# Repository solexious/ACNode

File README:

A design for the london hackspace tool access control system: http://wiki.london.hackspace.org.uk/view/Project:Tool_Access_Control

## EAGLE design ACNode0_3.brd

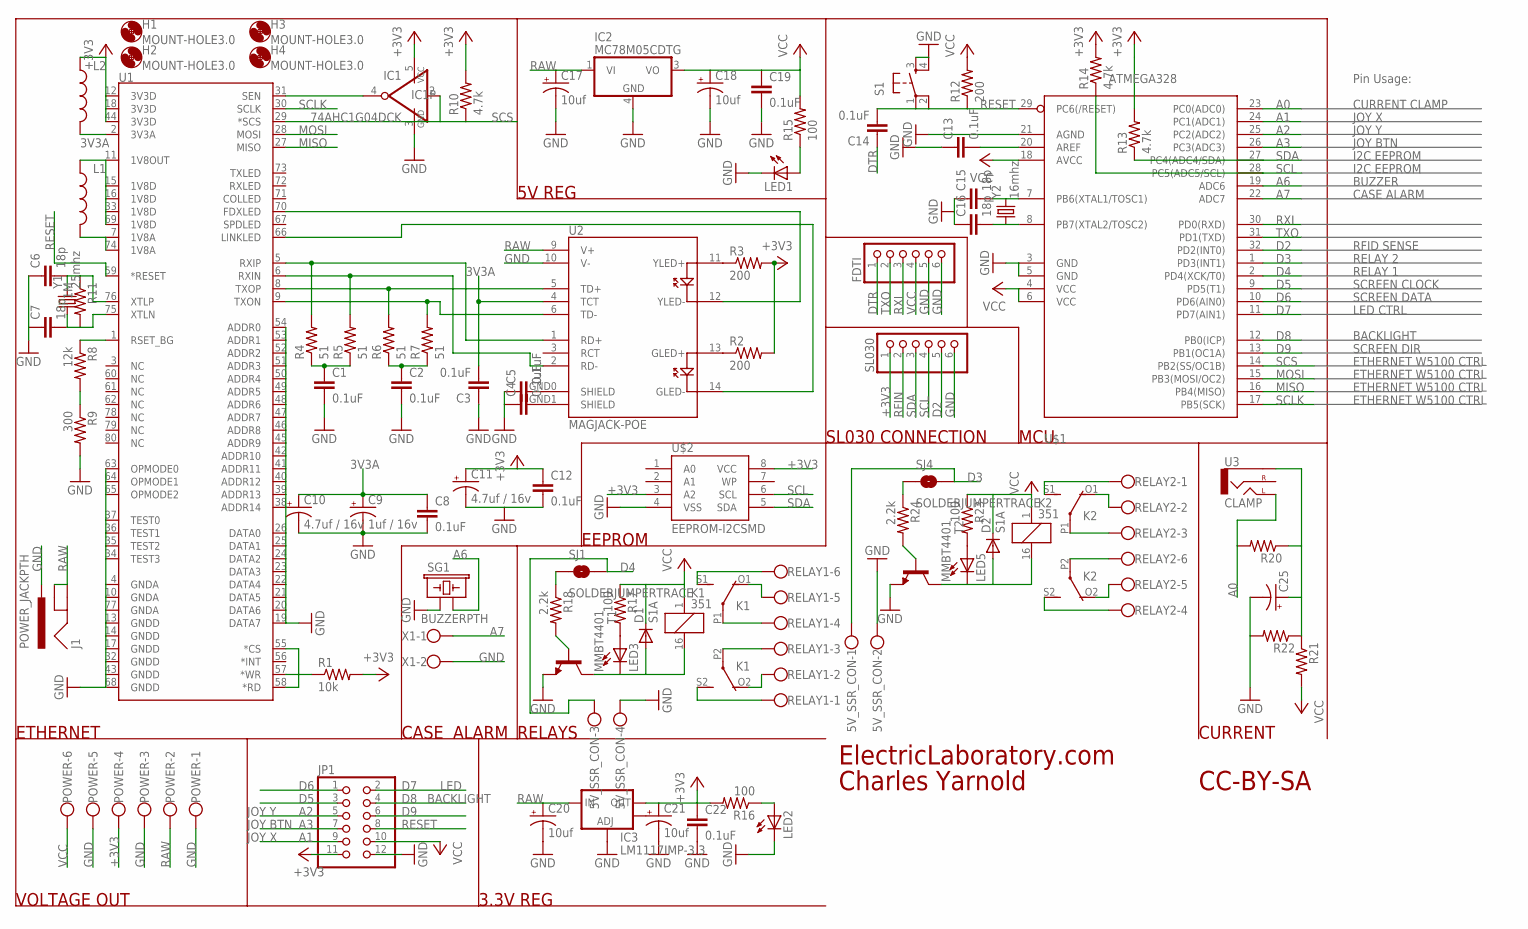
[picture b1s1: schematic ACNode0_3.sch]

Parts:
5V_SSR_CON: W237-4
C1, C2, C3, C4, C5, C8, C12, C13, C14, C19, C22: 0.1uF; 0603-CAP
C6, C7, C15, C16: 18p; 0603-CAP
C9: 1uf / 16v; EIA3216
C10, C11: 4.7uf / 16v; EIA3216
C17, C18, C20, C21: 10uf; EIA3216
C25: CAP_POL1206; EIA3216
D1, D2: S1A; DO-214AC
FDTI: PINHD-1X6; 1X06
H1, H2, H3, H4: MOUNT-HOLE3.0; 3,0
IC1: 74AHC1G04DCK; SC70-5
IC2: MC78M05CDTG; DPACK_3
IC3: LM1117IMP-3.3; SOT223
J1: POWER_JACKPTH; POWER_JACK_PTH
JP1: PINHD-2X6; 2X06
K1, K2: 351
L1, L2: INDUCTOR1206H*; INDUCTOR-1206
LED1, LED2, LED3, LED5: LED0603; LED-0603
POWER: W237-6
R1: 10k; 0603-RES
R2, R3, R12: 200; 0603-RES
R4, R5, R6, R7: 51; 0603-RES
R8: 12k; 0603-RES
R9: 300; 0603-RES
R10, R13, R14: 4.7k; 0603-RES
R11: 1M; 0603-RES
R15, R16, R17, R23: 100; 0603-RES
R18, R24: 2.2k; 0603-RES
R20, R21, R22: RESISTOR0603-RES; 0603-RES
RELAY1, RELAY2: W237-6
S1: TAC_SWITCHSMD; TACTILE_SWITCH_SMD
SG1: BUZZERPTH; BUZZER-12MM
SJ1, SJ4: SOLDERJUMPERTRACE; SJ_2S-TRACE
SL030: PINHD-1X6; 1X06
T1, T2: MMBT4401; SOT23-BEC
U1: W5100; LQFP-80
U2: MAGJACK-POE
U3: CLAMP; AUDIO-JACK
U$1: ATMEGA328; TQFP32-08
U$2: EEPROM-I2CSMD; SO08
X1: W237-102
Y1: 25mhz; HC49UP
Y2: 16mhz; HC49UP

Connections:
3V3A: C3.2, C8.1, C9.A (+), C10.A (+), L2.P$2 (2), U1.2 (3V3A), U2.4 (TCT)
+3V3: C11.A (+), C12.1, C21.A (+), C22.1, IC1.5 (VCC), IC3.2 (OUT), JP1.11, L2.P$1 (1), POWER.4, R1.2, R2.2, R3.2, R10.2, R13.2, R14.2, R16.2, SL030.1, U1.12 (3V3D), U1.18 (3V3D), U1.44 (3V3D), U$2.3 (A2), U$2.8 (VCC)
A0: R20.2, U3.TIP (LEFT), U$1.23 (PC0(ADC0))
A1: JP1.9, U$1.24 (PC1(ADC1))
A2: JP1.5, U$1.25 (PC2(ADC2))
A3: JP1.7, U$1.26 (PC3(ADC3))
A6: SG1.- (2), U$1.19 (ADC6)
A7: U$1.22 (ADC7), X1.1
D2: SL030.5, U$1.32 (PD2(INT0))
D3: 5V_SSR_CON.1, SJ4.2, U$1.1 (PD3(INT1))
D4: 5V_SSR_CON.3, SJ1.2, U$1.2 (PD4(XCK/T0))
D5: JP1.3, U$1.9 (PD5(T1))
D6: JP1.1, U$1.10 (PD6(AIN0))
D7: JP1.2, U$1.11 (PD7(AIN1))
D8: JP1.4, U$1.12 (PB0(ICP))
D9: JP1.6, U$1.13 (PB1(OC1A))
DTR: C14.1, FDTI.1
GND: 5V_SSR_CON.2, 5V_SSR_CON.4, C1.2, C2.2, C3.1, C4.1, C5.1, C6.1, C7.1, C8.2, C9.C (-), C10.C (-), C11.C (-), C12.2, C13.1, C15.1, C16.1, C17.C (-), C18.C (-), C19.2, C20.C (-), C21.C (-), C22.2, C25.C (-), FDTI.5, FDTI.6, IC1.3 (GND), IC2.4 (GND), IC3.1 (ADJ), J1.PWR, JP1.12, LED1.C, LED2.C, POWER.1, POWER.3, POWER.5, R9.2, R22.2, S1.3, S1.4, SG1.+ (1), SL030.6, T1.E, T2.E, U1.4 (GNDA), U1.10 (GNDA), U1.13 (GNDD), U1.14 (GNDD), U1.17 (GNDD), U1.19 (DATA7), U1.20 (DATA6), U1.21 (DATA5), U1.22 (DATA4), U1.23 (DATA3), U1.24 (DATA2), U1.25 (DATA1), U1.26 (DATA0), U1.32 (GNDD), U1.34 (TEST3), U1.35 (TEST2), U1.36 (TEST1), U1.37 (TEST0), U1.38 (ADDR14), U1.39 (ADDR13), U1.40 (ADDR12), U1.41 (ADDR11), U1.42 (ADDR10), U1.43 (GNDD), U1.45 (ADDR9), U1.46 (ADDR8), U1.47 (ADDR7), U1.48 (ADDR6), U1.49 (ADDR5), U1.50 (ADDR4), U1.51 (ADDR3), U1.52 (ADDR2), U1.53 (ADDR1), U1.54 (ADDR0), U1.63 (OPMODE0), U1.64 (OPMODE1), U1.65 (OPMODE2), U1.68 (GNDD), U1.77 (GNDA), U2.10 (V-), U$1.3 (GND), U$1.5 (GND), U$1.21 (AGND), U$2.4 (VSS), X1.2
MISO: U1.27 (MISO), U$1.16 (PB4(MISO))
MOSI: U1.28 (MOSI), U$1.15 (PB3(MOSI/OC2))
unnamed: IC1.4 (O), U1.31 (SEN)
unnamed: C13.2, U$1.20 (AREF)
unnamed: C2.1, R6.1, R7.1
unnamed: C1.1, R4.1, R5.1
unnamed: L1.P$2 (2), U1.7 (1V8A), U1.74 (1V8A)
unnamed: L1.P$1 (1), U1.11 (1V8OUT), U1.15 (1V8D), U1.16 (1V8D), U1.33 (1V8D), U1.69 (1V8D)
unnamed: R1.1, U1.55 (*CS), U1.57 (*WR), U1.58 (*RD)
unnamed: R8.2, R9.1
unnamed: R6.2, U1.8 (TXOP), U2.5 (TD+)
unnamed: R7.2, U1.9 (TXON), U2.6 (TD-)
unnamed: R4.2, U1.5 (RXIP), U2.1 (RD+)
unnamed: R5.2, U1.6 (RXIN), U2.2 (RD-)
unnamed: R3.1, U2.11 (YLED+)
unnamed: R2.1, U2.13 (GLED+)
unnamed: R8.1, U1.1 (RSET_BG)
unnamed: U1.70 (FDXLED), U2.12 (YLED-)
unnamed: U1.66 (LINKLED), U2.14 (GLED-)
unnamed: C5.2, U2.GND0 (SHIELD)
unnamed: C4.2, U2.GND1 (SHIELD)
unnamed: C7.2, R11.2, U1.75 (XTLN), Y1.1
unnamed: C6.2, R11.1, U1.76 (XTLP), Y1.2
unnamed: C15.2, U$1.7 (PB6(XTAL1/TOSC1)), Y2.2
unnamed: K2.P1, RELAY2.3
unnamed: C16.2, U$1.8 (PB7(XTAL2/TOSC2)), Y2.1
unnamed: K1.S2 (S), RELAY1.1
unnamed: LED1.A, R15.1
unnamed: K1.O2 (O), RELAY1.2
unnamed: LED2.A, R16.1
unnamed: K1.P2, RELAY1.3
unnamed: K1.P1, RELAY1.4
unnamed: K1.O1 (O), RELAY1.5
unnamed: K1.S1 (S), RELAY1.6
unnamed: LED3.A, R17.2
unnamed: D1.A, K1.16 (2), LED3.C, T1.C
unnamed: R18.2, T1.B
unnamed: K2.P2, RELAY2.6
unnamed: R18.1, SJ1.1
unnamed: C25.A (+), R20.1, R21.1, R22.1, U3.SLEEVE
unnamed: K2.S2 (S), RELAY2.4
unnamed: K2.O2 (O), RELAY2.5
unnamed: K2.O1 (O), RELAY2.2
unnamed: K2.S1 (S), RELAY2.1
unnamed: LED5.A, R23.2
unnamed: D2.A, K2.16 (2), LED5.C, T2.C
unnamed: R24.2, T2.B
unnamed: R24.1, SJ4.1
RAW: C17.A (+), C20.A (+), IC2.1 (VI), IC3.3 (IN), J1.GND, J1.GNDBREAK, POWER.2, U2.9 (V+)
RESET: C14.2, JP1.8, R12.1, S1.1, S1.2, U1.59 (*RESET), U$1.29 (PC6(/RESET))
RFIN: SL030.2
RXI: FDTI.3, U$1.30 (PD0(RXD))
SCL: R14.1, SL030.4, U$1.28 (PC5(ADC5/SCL)), U$2.6 (SCL)
SCLK: U1.30 (SCLK), U$1.17 (PB5(SCK))
SCS: IC1.2 (I), R10.1, U1.29 (*SCS), U$1.14 (PB2(SS/OC1B))
SDA: R13.1, SL030.3, U$1.27 (PC4(ADC4/SDA)), U$2.5 (SDA)
TXO: FDTI.2, U$1.31 (PD1(TXD))
VCC: C18.A (+), C19.1, D1.C, D2.C, FDTI.4, IC2.3 (VO), JP1.10, K1.1, K2.1, POWER.6, R12.2, R15.2, R17.1, R21.2, R23.1, U$1.4 (VCC), U$1.6 (VCC), U$1.18 (AVCC)

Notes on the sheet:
ElectricLaboratory.com
Charles Yarnold
CC-BY-SA
ETHERNET
MCU
5V REG
EEPROM
SL030 CONNECTION
VOLTAGE OUT
3.3V REG
RELAYS
CURRENT
CASE
ALARM
Pin Usage:
I2C EEPROM
ETHERNET W5100 CTRL
CURRENT CLAMP
CASE ALARM
BUZZER
JOY X
JOY Y
JOY BTN
RFID SENSE
RELAY 1
RELAY 2
LED
BACKLIGHT
SCREEN DATA
SCREEN CLOCK
SCREEN DIR
LED CTRL

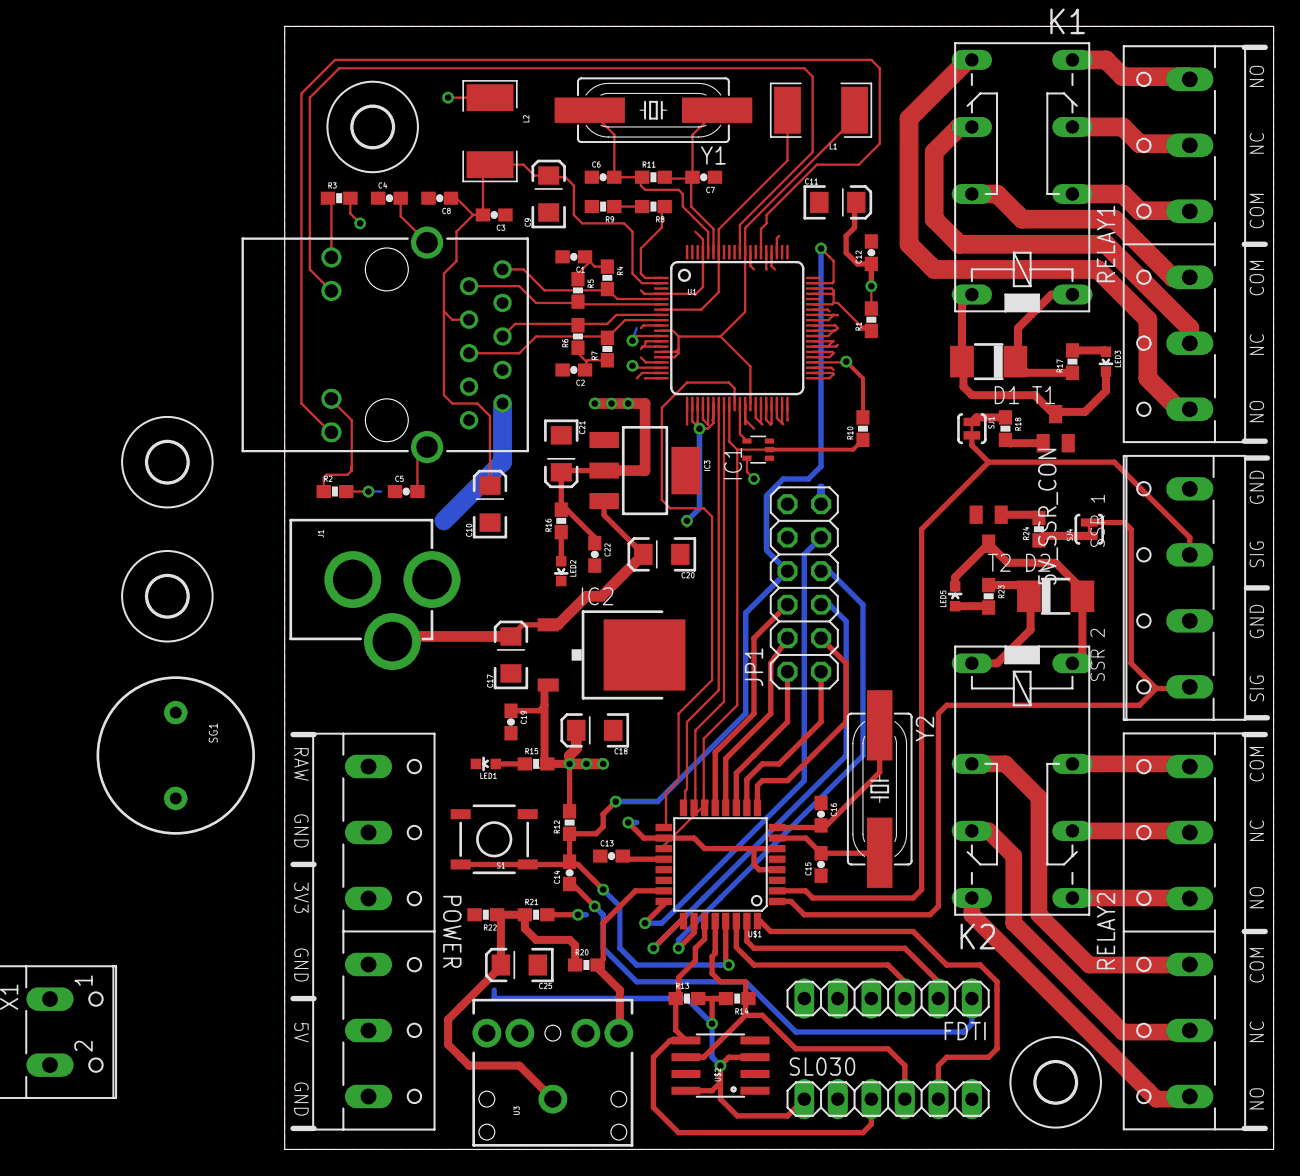
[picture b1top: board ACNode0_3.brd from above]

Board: 2 copper layers, 74.9 x 85.1 mm, 85 parts (0 on the bottom side), 75 nets.

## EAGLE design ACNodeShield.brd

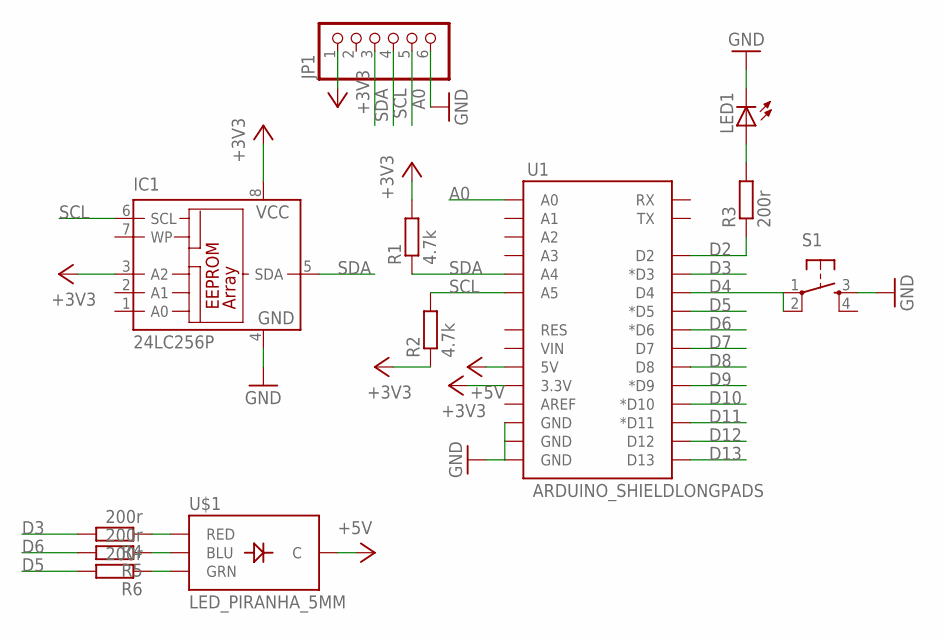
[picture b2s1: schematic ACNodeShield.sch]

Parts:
IC1: 24LC256P; DIL8
JP1: PINHD-1X6; 1X06
LED1: LED5MM
R1, R2: 4.7k; 0204/7
R3, R4, R5, R6: 200r; 0204/7
S1: TAC_SWITCHPTH; TACTILE-PTH
U1: ARDUINO_SHIELDLONGPADS; DUEMILANOVE_SHIELD_LONGPADS
U$1: LED_PIRANHA_5MM

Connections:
+3V3: IC1.3 (A2), IC1.8 (VCC), JP1.1, R1.2, R2.1, U1.3.3V
+5V: U1.5V, U$1.- (C)
A0: JP1.5, U1.A0
D2: R3.1, U1.D2
D3: R4.2, U1.D3 (*D3)
D4: S1.1, S1.2, U1.D4
D5: R6.2, U1.D5 (*D5)
D6: R5.2, U1.D6 (*D6)
D7: U1.D7
D8: U1.D8
D9: U1.D9 (*D9)
D10: U1.D10 (*D10)
D11: U1.D11 (*D11)
D12: U1.D12
D13: U1.D13
GND: IC1.4 (GND), JP1.6, LED1.K (C), S1.3, U1.GND@0 (GND), U1.GND@1 (GND), U1.GND@2 (GND)
unnamed: R4.1, U$1.R (RED)
unnamed: LED1.A, R3.2
unnamed: R5.1, U$1.B (BLU)
unnamed: R6.1, U$1.G (GRN)
SCL: IC1.6 (SCL), JP1.4, R2.2, U1.A5
SDA: IC1.5 (SDA), JP1.3, R1.1, U1.A4

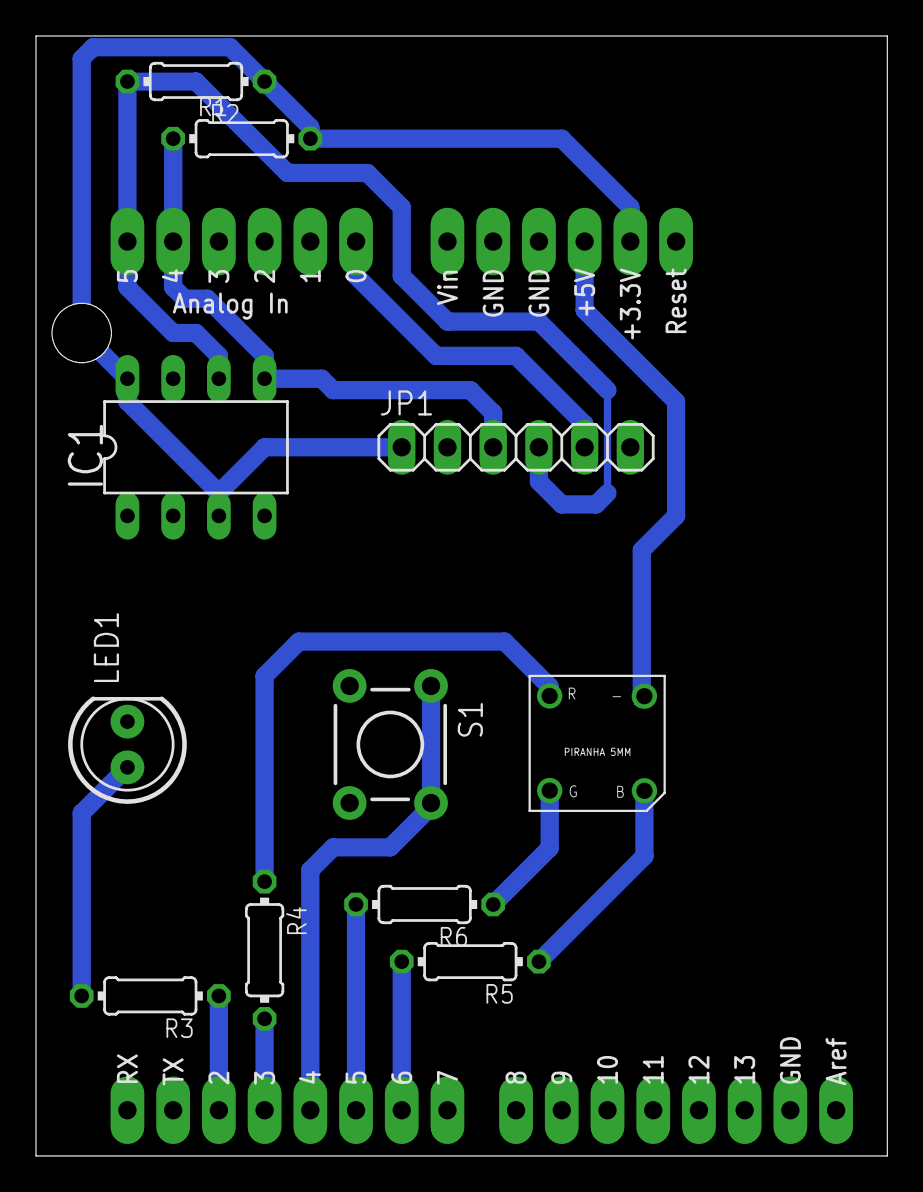
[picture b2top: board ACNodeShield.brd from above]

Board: 2 copper layers, 47.3 x 62.2 mm, 12 parts (0 on the bottom side), 15 nets.

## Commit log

2012-02-05 Add pdf version
2012-02-06 Initial wiznet controller design
2012-02-07 Add basic MCU
2012-02-07 Add pullup resistors, FDTI port and resize resistors
2012-02-08 Add 5v regulator and SL030 connector
2012-02-08 Label those schematics
2012-02-08 Add 3v3 reg and voltage out
2012-02-08 Add button, led and relay
2012-02-08 Add controls, tidy up, add w5100 reset
2012-02-10 First route attempt
2012-02-10 Make readme
2012-02-10 update sch
2012-02-10 Correct DRC
2012-02-11 Correct SL030 pins
2012-02-11 Draft of proto shield
2014-01-07 Full schematic
2014-02-16 layout sans poe

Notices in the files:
parts and their libraries:
SparkFun-DigitalIC: Licensing: CC v3.0 Share-Alike You are welcome to use this library for commercial purposes.
